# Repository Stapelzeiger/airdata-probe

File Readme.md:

# Airdata Probe

## Ports

## PCB

[Schematic](pcb/airdata.pdf)

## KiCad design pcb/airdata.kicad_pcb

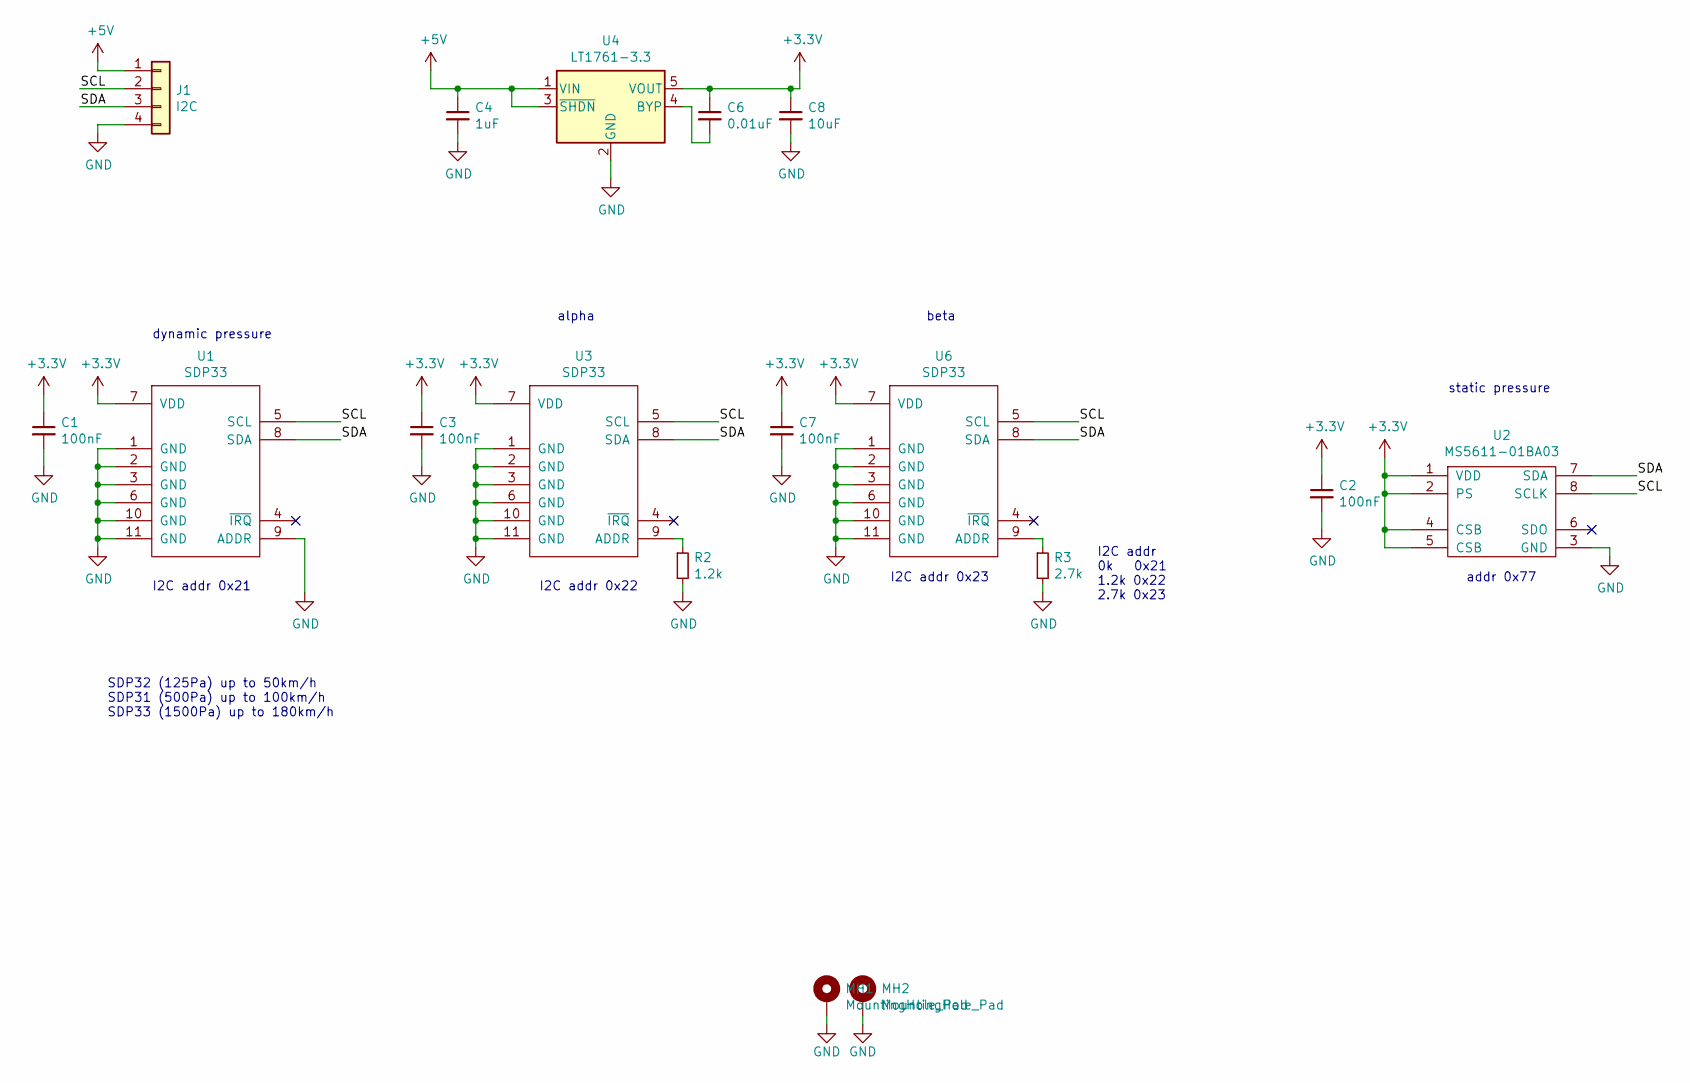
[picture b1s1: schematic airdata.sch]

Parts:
C1, C2, C3, C7: 100nF; C_0603_1608Metric
C4: 1uF; C_0603_1608Metric
C6: 0.01uF; C_0603_1608Metric
C8: 10uF; C_0603_1608Metric
J1: I2C; JST_GH_SM04B-GHS-TB_1x04-1MP_P1.25mm_Horizontal
MH1, MH2: MountingHole_Pad; MountingHole_2.2mm_M2_Pad_Via
R2: 1.2k; R_0603_1608Metric
R3: 2.7k; R_0603_1608Metric
U1, U3, U6: SDP33; SDP3x
U2: MS5611-01BA03; MS5611-01BA
U4: LT1761-3.3; TSOT-23-5

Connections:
+3V3: C1.1, C2.1, C3.1, C6.1, C7.1, C8.1, U1.7 (VDD), U2.1 (VDD), U2.2 (PS), U2.4 (CSB), U2.5 (CSB), U3.7 (VDD), U4.5 (VOUT), U6.7 (VDD)
+5V: C4.1, J1.1, U4.1 (VIN), U4.3 (~SHDN)
/SCL: J1.2, U1.5 (SCL), U2.8 (SCLK), U3.5 (SCL), U6.5 (SCL)
/SDA: J1.3, U1.8 (SDA), U2.7 (SDA), U3.8 (SDA), U6.8 (SDA)
GND: C1.2, C2.2, C3.2, C4.2, C7.2, C8.2, J1.4, MH1.1, MH2.1, R2.2, R3.2, U1.1 (GND), U1.2 (GND), U1.3 (GND), U1.6 (GND), U1.9 (ADDR), U1.10 (GND), U1.11 (GND), U2.3 (GND), U3.1 (GND), U3.2 (GND), U3.3 (GND), U3.6 (GND), U3.10 (GND), U3.11 (GND), U4.2 (GND), U6.1 (GND), U6.2 (GND), U6.3 (GND), U6.6 (GND), U6.10 (GND), U6.11 (GND)
unnamed: C6.2, U4.4 (BYP)
unnamed: R2.1, U3.9 (ADDR)
unnamed: R3.1, U6.9 (ADDR)

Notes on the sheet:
I2C addr 0k 0x21 1.2k 0x22 2.7k 0x23
I2C addr 0x23
addr 0x77
alpha
beta
dynamic pressure
static pressure
SDP32 (125Pa) up to 50km/h SDP31 (500Pa) up to 100km/h SDP33 (1500Pa) up to 180km/h
I2C addr 0x22
I2C addr 0x21

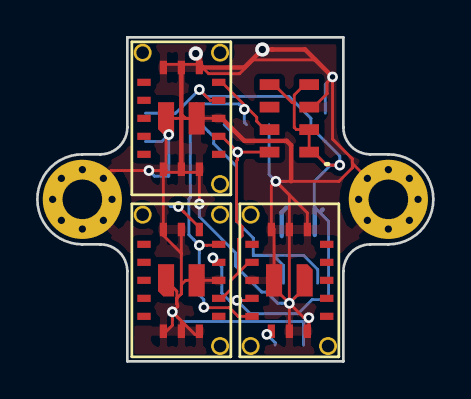
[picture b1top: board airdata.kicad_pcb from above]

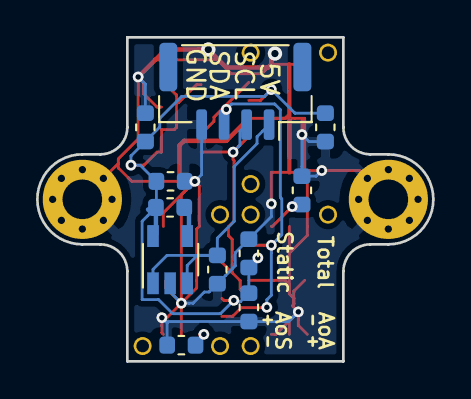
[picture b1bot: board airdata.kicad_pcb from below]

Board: 2 copper layers, 22.0 x 18.0 mm, 17 parts (11 on the bottom side), 8 nets.

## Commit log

2022-06-05 airdata probe
2022-06-05 Readme
